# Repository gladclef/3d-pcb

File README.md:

# 3d-pcb
Converts KiCad gencad ".cad" files into 3d printable circuit boards. I want to be able to design a PCB, print it the same day, and iterate.

## Examples

Small example [hello_light](/examples/hello_light/):

## Usage

#### Installation

1. [Download and install python](https://www.python.org/downloads/)
2. [Download and install git](https://git-scm.com/downloads)
3. Create a new directory to download this project into. For example `%USERPROFILE%\AppData\Local\3D-PCB` on Windows or `~/prg/3D-PCB` on Linux/Mac.
4. Open a terminal in the newly created directory. On Windows start git bash. On Linux/Mac use the shortcut `Win+Space`/`Cmd+Space` and type "terminal". Then use the "cd" command to move to the newly created directory, for example "cd ~/AppData/Local/3D-PCB".
5. Download the project by running "git clone https://github.com/gladclef/3d-pcb.git" in the terminal.

#### 3D-PCB Creation

The steps to produce a 3D-PCB are:

1. Design schematic and layout
2. Run "python src/Board.py" from the downloaded git directory.
3. Create a new Blender project
    a. Import the traces, vias, and components
    b. Size a board to match
    c. Boolean-subtract the traces, vias, and components
    d. Export the ready-to-print board
4. Print the 3D-PCB
5. Fill the traces with 24 AWG tinned copper wire
6. Solder in the components

## Limitations

Below is a list of known limitations to layouts based on th current state of the project:

- Limited to 2 layers
- KiCad "GenCad" export files supported
- No forking traces (traces must go from one through-hole to another, not from a trace to a through-hole)
- No sharp bends (90 degree bends are OK)
- Trace connections to through-holes should provide ~0.5mm of space North of the trace.
- Vias [aren't currently supported](https://github.com/gladclef/3d-pcb/issues/1)
- Through-hole components only

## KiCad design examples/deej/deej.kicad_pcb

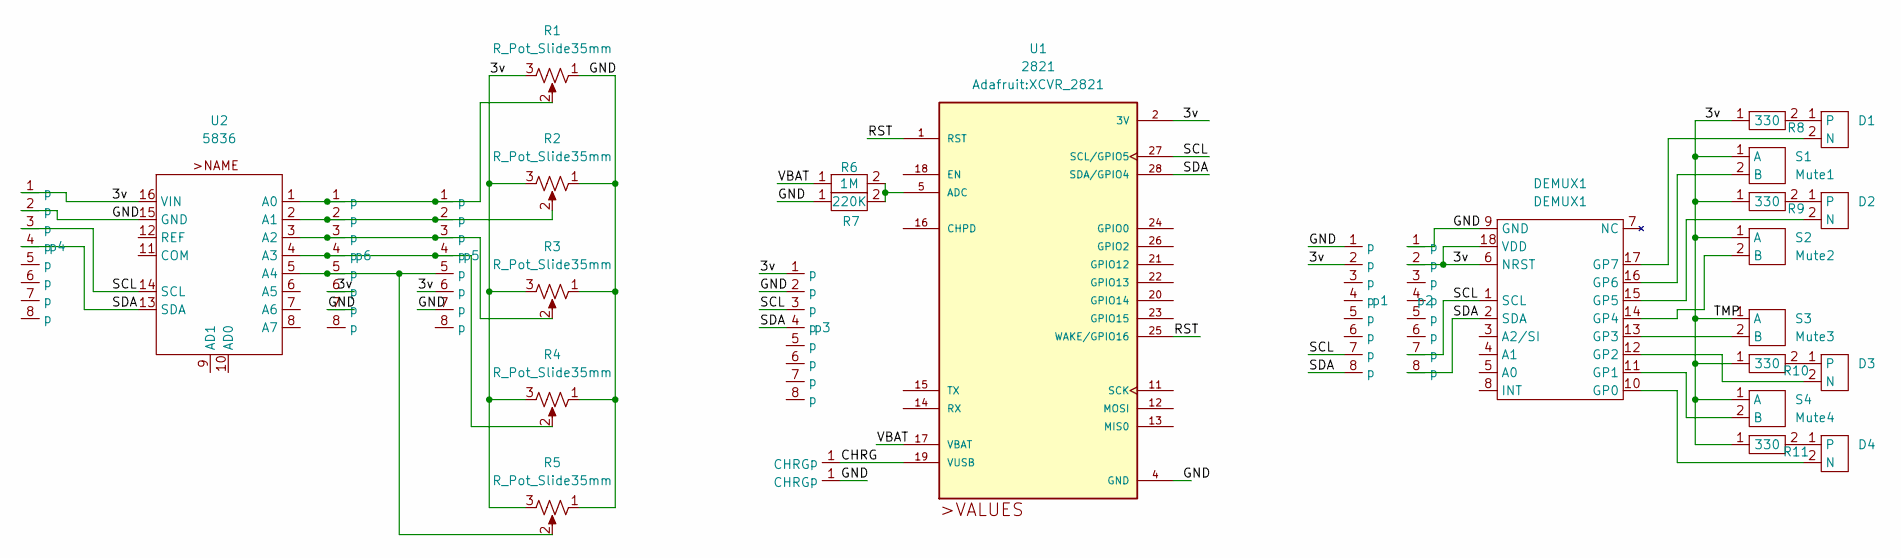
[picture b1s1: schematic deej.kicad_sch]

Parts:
D1, D2, D3, D4: LED_299
DEMUX1: DEMUX1; DEMUX_MCP23008_593
R1, R2, R3, R4, R5: R_Pot_Slide35mm; R_LinPot_C2031N
R6: 1M; Resistor_2784
R7: 220K; Resistor_2784
R8, R9, R10, R11: 330; Resistor_2784
S1: Mute1; SWITCH_367
S2: Mute2; SWITCH_367
S3: Mute3; SWITCH_367
S4: Mute4; SWITCH_367
U1: 2821; XCVR_2821
U2: 5836; ADC_5836
p1, p2, p3, p4, p5, p6: Through Hole 0.1in 8 Pin
p7, p8: CHRG; Through Hole 0.1in 1 Pin

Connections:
/3v: DEMUX1.6 (NRST), DEMUX1.18 (VDD), R1.3, R2.3, R3.3, R4.3, R5.3, R8.1, R9.1, R10.1, R11.1, S1.1 (A), S2.1 (A), S3.1 (A), S4.1 (A), U1.2 (3V), U2.16 (VIN), p1.2 (p), p2.2 (p), p3.1 (p), p4.1 (p), p5.6 (p), p6.6 (p)
/CHRG: U1.19 (VUSB), p7.1 (p)
/GND: DEMUX1.9 (GND), R1.1, R2.1, R3.1, R4.1, R5.1, R7.1, U1.4 (GND), U2.15 (GND), p1.1 (p), p2.1 (p), p3.2 (p), p4.2 (p), p5.7 (p), p6.7 (p), p8.1 (p)
/RST: U1.1 (RST), U1.25 (WAKE/GPIO16)
/SCL: DEMUX1.1 (SCL), U1.27 (SCL/GPIO5), U2.14 (SCL), p1.7 (p), p2.7 (p), p3.3 (p), p4.3 (p)
/SDA: DEMUX1.2 (SDA), U1.28 (SDA/GPIO4), U2.13 (SDA), p1.8 (p), p2.8 (p), p3.4 (p), p4.4 (p)
/VBAT: R6.1, U1.17 (VBAT)
unnamed: D1.2 (N), DEMUX1.17 (GP7)
unnamed: D1.1, R8.2
unnamed: D2.2 (N), DEMUX1.15 (GP5)
unnamed: D2.1, R9.2
unnamed: D3.2 (N), DEMUX1.12 (GP2)
unnamed: D3.1, R10.2
unnamed: D4.2 (N), DEMUX1.10 (GP0)
unnamed: D4.1, R11.2
unnamed: DEMUX1.11 (GP1), S4.2 (B)
unnamed: DEMUX1.13 (GP3), S3.2 (B)
unnamed: DEMUX1.14 (GP4), S2.2 (B)
unnamed: DEMUX1.16 (GP6), S1.2 (B)
unnamed: R6.2, R7.2, U1.5 (ADC)
unnamed: R1.2, U2.1 (A0), p5.1 (p), p6.1 (p)
unnamed: R2.2, U2.2 (A1), p5.2 (p), p6.2 (p)
unnamed: R3.2, U2.3 (A2), p5.3 (p), p6.3 (p)
unnamed: R4.2, U2.4 (A3), p5.4 (p), p6.4 (p)
unnamed: R5.2, U2.5 (A4), p5.5 (p), p6.5 (p)

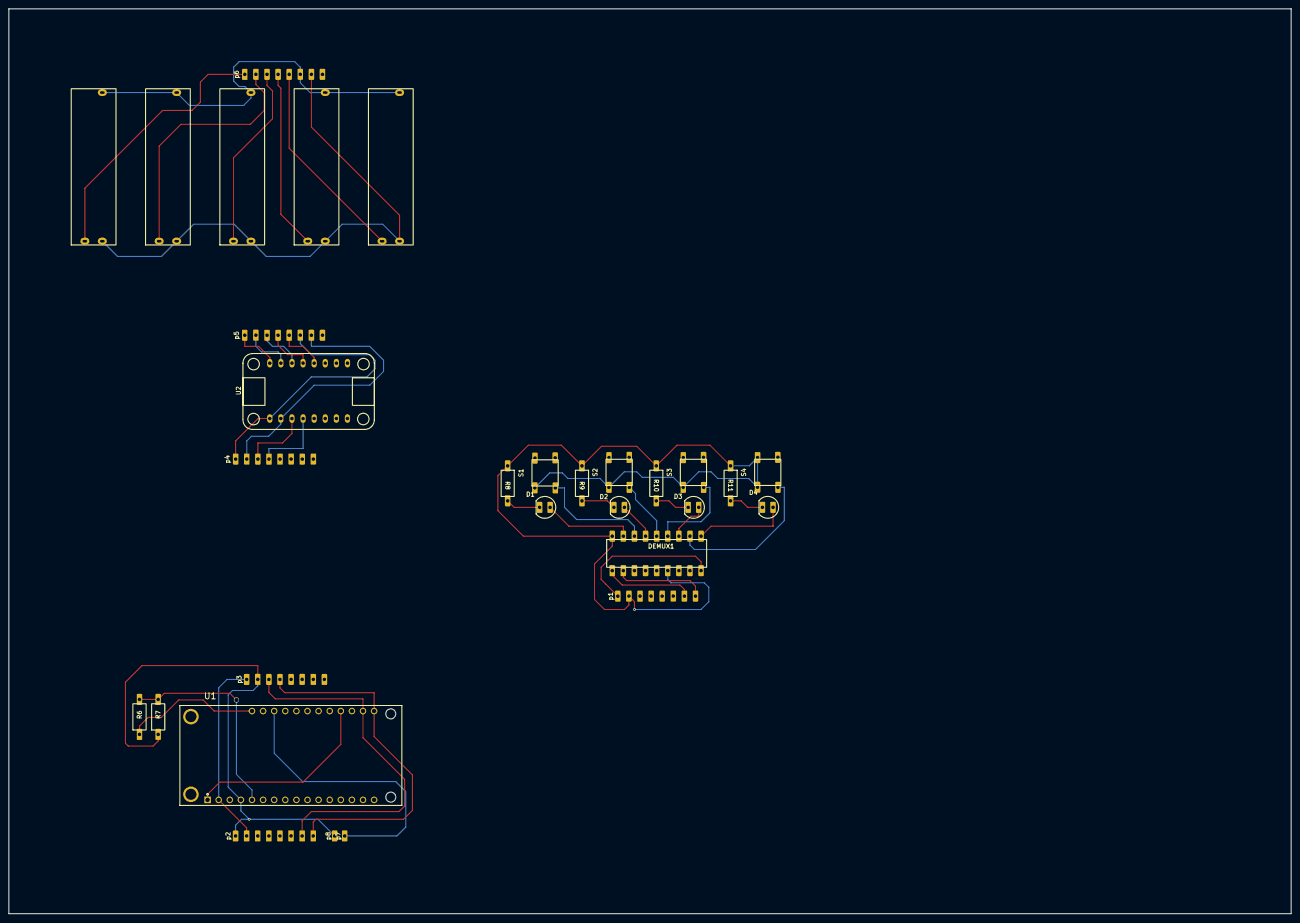
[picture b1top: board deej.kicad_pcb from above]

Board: 4 copper layers, 293.4 x 207.0 mm, 30 parts (0 on the bottom side), 25 nets.

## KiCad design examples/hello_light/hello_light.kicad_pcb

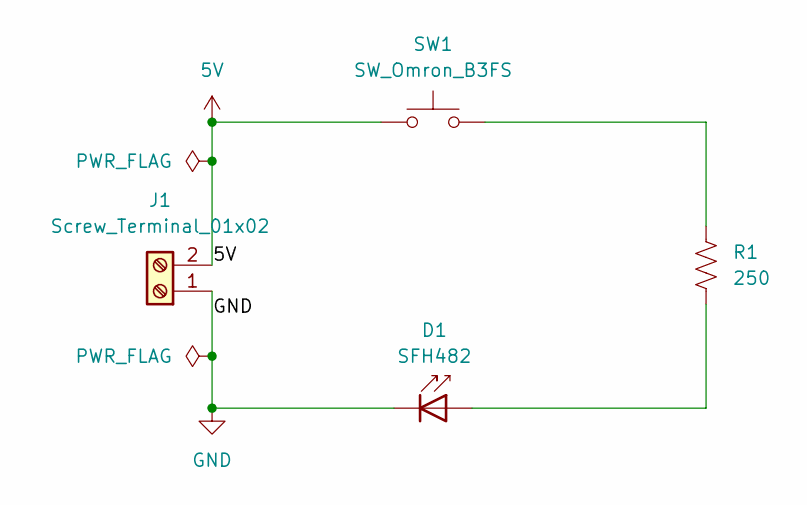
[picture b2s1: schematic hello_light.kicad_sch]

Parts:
D1: SFH482; LED_D5.0mm
J1: Screw_Terminal_01x02; TerminalBlock_4Ucon_1x02_P3.50mm_Horizontal
R1: 250; R_Axial_DIN0309_L9.0mm_D3.2mm_P12.70mm_Horizontal
SW1: SW_Omron_B3FS; SW_TH_Tactile_Omron_B3F-10xx

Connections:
5V: J1.2, SW1.1
GND: D1.1 (K), J1.1
unnamed: D1.2 (A), R1.2
unnamed: R1.1, SW1.2

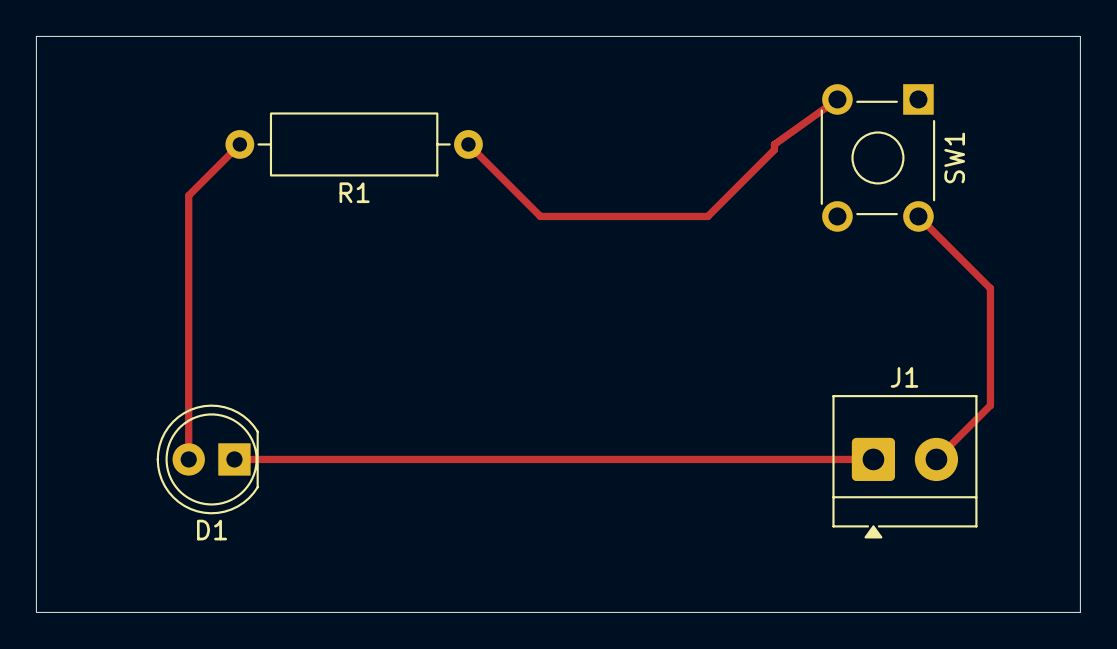
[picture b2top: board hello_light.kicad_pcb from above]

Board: 2 copper layers, 58.0 x 32.0 mm, 4 parts (0 on the bottom side), 4 nets.

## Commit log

2025-05-31 Basic structure is set up for creating traces out of 2d shapes
2025-06-04 moving Trace to SingleTrace
2025-06-04 solidpython2 crashes, vtkbool doesn't bool good
2025-06-04 in PipeShape add triangles by default
2025-06-05 started on TraceCorner class, general code quality improvements
2025-06-07 basic implementation of TraceCorner.get_arc_seg_intersections() is working for a simple case
2025-06-07 reorganization
2025-06-09 trace corners is producing good arc centers and center line points
2025-06-09 generalize TraceCorner -> PathCorner so that it can be applied to more than just traces
2025-06-10 AbstractPath -> Path
2025-06-10 more organization
2025-06-15 introduced new classes Line, LineSegment, Path, and PathCorner, and updated code to use new classes
2025-06-16 add method Line.is_parallel_to(), fix LineSegment.intersection
2025-06-16 documentation
2025-06-16 add VtkPointGroup, add vtk_tools.join_with_quads(), fill out TraceCorner, move rotation and translation to PipeShape.oriented_points()
2025-06-16 override "reversed()" method on LineSegment
2025-06-19 order the xy points as they are used to generate a path
2025-06-19 build a trace from a gencad file exported from kicad
2025-06-19 build all traces in a gencad file
2025-06-19 rename BoardTraces -> Board
2025-06-19 add new Component class and associated classes
2025-06-19 mostly fixed Component from_cad_file(), add Line class
2025-06-20 fix parsing and drawing of components
2025-06-20 add Arc and Circle support for component outlines
2025-06-20 add pins to generated mesh
2025-06-20 add new default pipe shape PipeBasicCircle
2025-06-21 many small fixes
2025-06-21 working normals assignment
2025-06-22 add vias with an offset to traces
2025-06-22 make the trace corner radius globally configurable
2025-09-20 add line class for improved traceability and debug capability, allow most classes to return multiple instances in their "from_cad_file" methods
2025-09-20 removing unused imports
2025-09-20 fix regex patterns
2025-09-20 rework SingleTrace to auto-detect individual traces within a single route, fix region_end in CadFileHelper
2025-09-20 update directory for testing the larger file
2025-09-21 add option to only keep traces and trace vias for a specified layer
2025-09-21 fix edge groups for unnamed layers
2025-09-21 fix solo edges
2025-09-21 match _all_ traces
2025-09-21 add small example PCB
2025-09-21 add examples/hello_light images, update README, fix code to support example hello_light
2025-09-21 add vias_example.png
2025-09-21 Update README.md with link to #1
2025-09-21 use a class to keep track of edges instead of tuples during cad file processing
2025-09-21 remove unused files
2025-09-21 add second example "deej"
2025-09-21 ignore KiCad lock files
2025-09-22 fix typing in Path
2025-09-22 add cleanup() methods to deal with small trace segments
2025-09-22 flesh out examples
2025-09-23 updated deej example with traces for input power
2025-09-27 fix deej pcb design
2025-09-27 add DEFAULT_WIRE_DIAMETER and CIRCLE_RESOLUTION as global parameters
2025-09-27 fix debug message
2025-09-27 add pcb stls for deej example, update blender file
2025-10-05 add MCP23008 GPIO over I2C chip
2025-10-06 add Point class, move all x,y pairs to a Point representation
2025-10-06 fix issue where points really should be coincident but they aren't quite
2025-10-06 parse inline vias of routes
2025-10-10 zero-based indexing
2025-10-18 more fixes for Point class
2025-10-18 more zero-based indexing
2025-10-18 reorder _xy_points and _xypntindicies_2_segments on the fly, use _TraceLine instead of tuples
2025-10-18 simplifications
2025-10-18 fix trace corners in cleanup_short_traces
2025-10-18 add support for branching traces
2025-10-20 update unit tests
2025-10-20 actually support reversed lines
2025-10-20 code reorganization for SingleTrace.from_cad_file()
2025-10-25 fix Via.from_cad_file()
2025-10-25 add support for branching vias
2025-10-25 fix single edge traces
2025-10-25 refinement of INF_THRESH
2025-10-25 adjust pins back along their closest edge
2025-10-26 use the segment that is a decent distance away as a way of avoiding tiny segments at the end point
2025-10-26 infinity is getting kinda small
2025-11-08 update Path and LineSegment and SingleTrace to use segments instead of xy point indicies
2025-11-08 move TraceLine into its own file, inherit from LineSegment
2025-11-08 track the route name when loading a trace from a cad file
2025-11-08 add Via.via_diameter(), add Via.draw()
2025-11-08 accept PipeRect as a non-debug shape
2025-11-08 add print_mode option, working on adjust_ends_for_conductive_filament() method
2025-11-10 fix setters for is_end, is_solo, and is_inner_edge
2025-11-10 add lots of checks to ensure that the structure of SingleTrace is correct
2025-11-11 add remove_segment(), get_previous_segment(), and get_next_segment() methods
2025-11-11 more checks, more fixes
2025-11-11 comments and print statements
2025-11-11 more fixes
2025-11-22 fix outdated code that got missed during the rework
2025-11-22 fix line direction flip
2025-11-22 fix 'get_segment_at_distance' method inside _get_pins_adjusted()
2025-11-22 add block and save_path options to draw_board() method
2025-11-23 include fline in all LineSegment class constructors
2025-11-23 create class from class type in Line
2025-11-26 update Line class to use two points as the basic representation
2025-11-29 deal with tiny traces
2025-11-29 fix Line.xy property
2025-11-29 add extra checks on Line.xy0 and line.xy1 setters
2025-11-30 split out SingleTrace class based on how it should make adjustments for the manufacturing type
